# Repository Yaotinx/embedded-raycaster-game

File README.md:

# Real-Time Embedded 3D Raycaster Game

An ARM Cortex-M0+ based 3D Wolfenstein-style raycaster featuring real-time rendering on an ST7735 TFT display via SPI, custom fixed-point mathematics, and ISR-driven audio and control systems.

---

## 📌 Project Overview
This project implements a full 3D raycasting engine on a resource-constrained ARM Cortex-M0+ microcontroller without hardware floating-point support. The system uses fixed-point arithmetic to achieve a smooth 30Hz target render loop while handling simultaneous user inputs and hardware-driven audio.

---

## ⚙️ Technical Highlights

* **Fixed-Point Raycasting Engine:** Custom Digital Differential Analysis (DDA) ray marching and sprite rendering optimized for high-frame-rate rendering on a 128x160 ST7735 LCD display.
* **Interrupt-Driven Subsystems:** ISR-synchronized ADC sampling for analog joystick, potentiometer, and push-button controls to minimize input latency.
* **Audio & FSM Logic:** Dual-timer ISR DAC audio playback paired with a 4-state Finite State Machine (FSM) controlling game loops, dynamic difficulty scaling, and a randomized reward FIFO.
* **Graphics & Localization:** Custom font rendering supporting localized English and Japanese glyphs for game HUDs and menus.

---

## 🛠️ Hardware & Pinout Setup

* **Microcontroller:** ARM Cortex-M0+ (TI MSPM0)
* **Display:** ST7735 128x160 TFT Display (SPI Protocol)
* **Inputs:** 2-Axis Analog Joystick (ADC), Potentiometer (ADC), Direct Push Buttons
* **Audio:** R-2R Ladder DAC Output connected to an audio amplifier/speaker

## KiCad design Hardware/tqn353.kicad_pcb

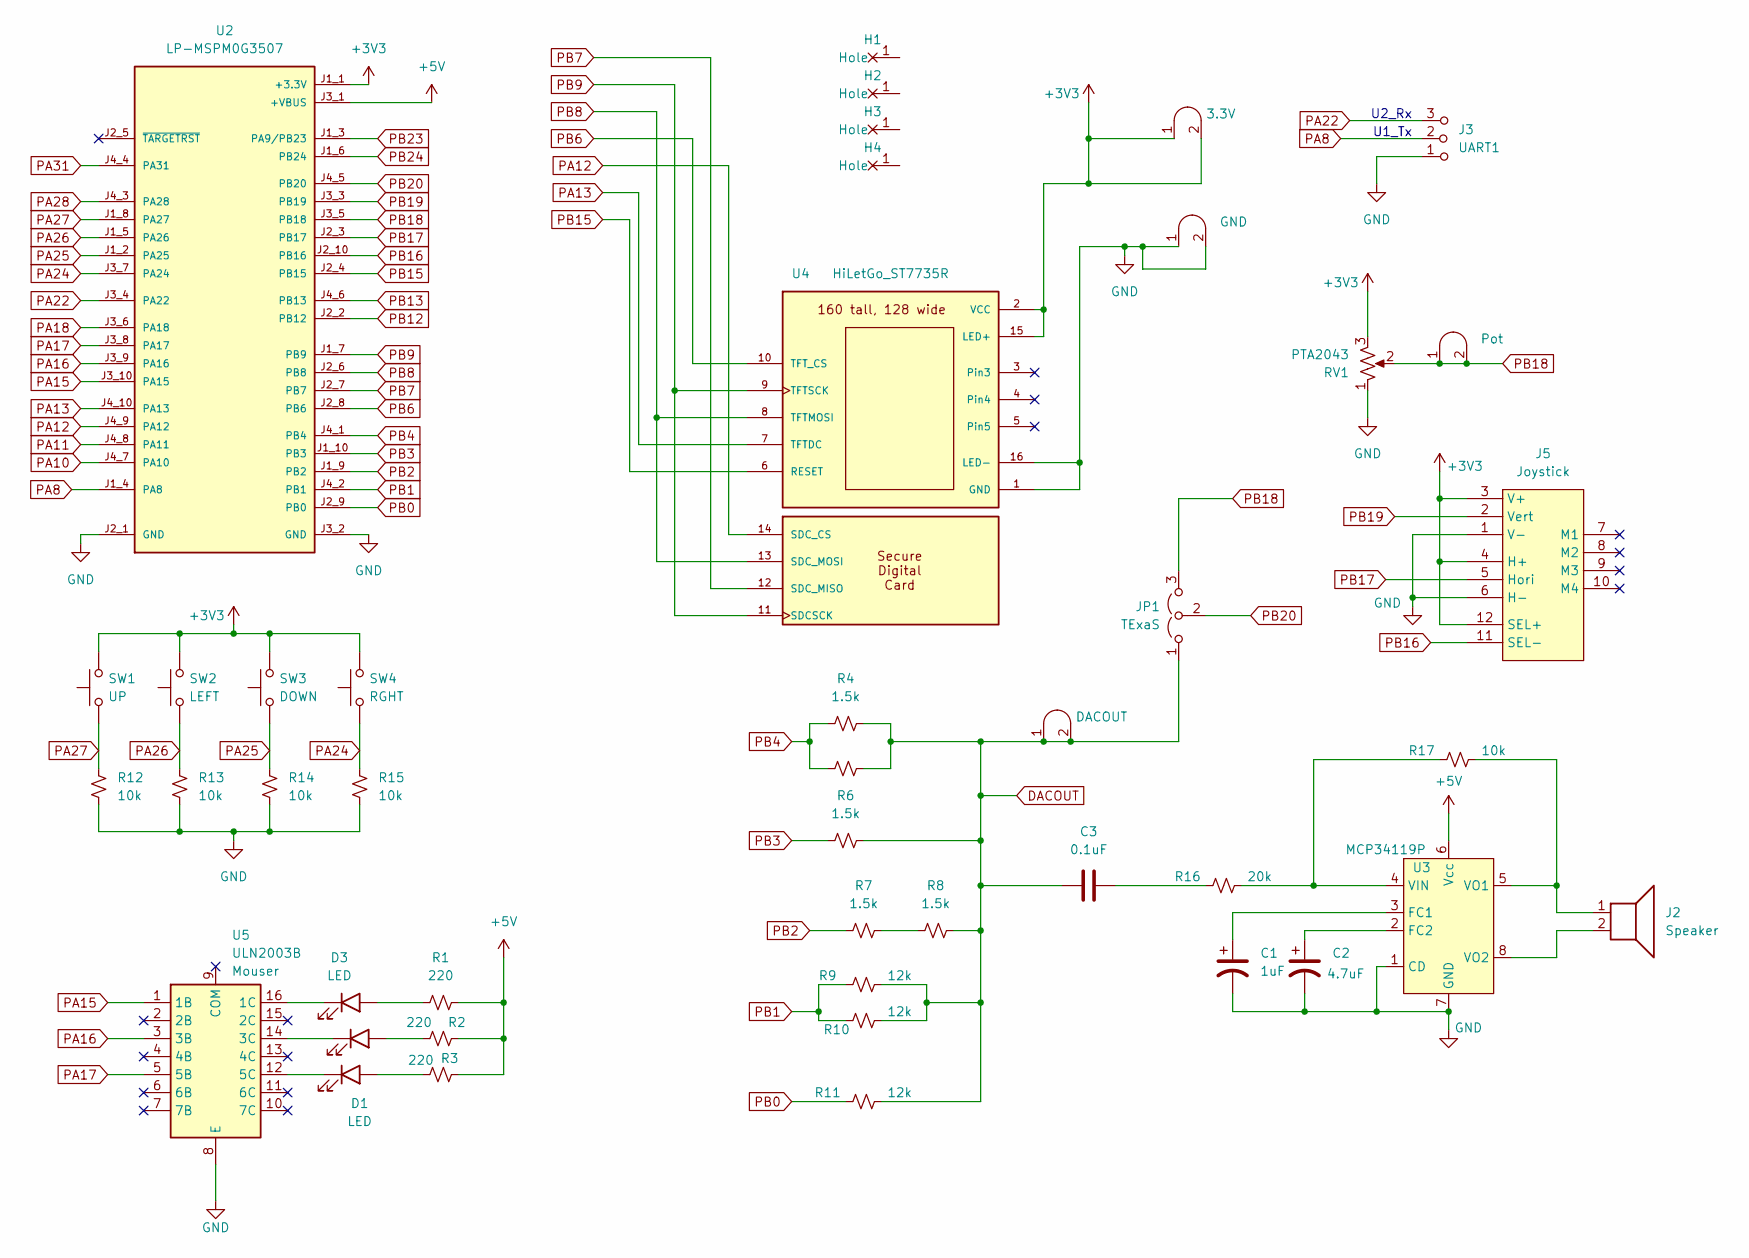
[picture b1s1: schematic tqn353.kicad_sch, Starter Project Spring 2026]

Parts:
C1: 1uF; CP_Radial_Tantal200mil
C2: 4.7uF; CP_Radial_Tantal200mil
C3: 0.1uF; C_Axial_200mil
D1, D2, D3: LED; LED_D5.0mm
H1, H2, H3, H4: MountingHole_4_40
J2: Speaker; PinHeader_1x02_P2.54mm_Vertical
J3: UART1; PinHeader_1x03_P2.54mm_Vertical
J4: Pot; Testpoint_1x02_P2.54mm
J5: Joystick; SparkfunJoystick
J6: GND; Testpoint_1x02_P2.54mm
J7: DACOUT; Testpoint_1x02_P2.54mm
JP1: TExaS; PinHeader_1x03_P2.54mm_Vertical
R1, R2, R3: 220; R_Axial_DIN0204_L3.6mm_D1.6mm_P7.62mm_Horizontal
R4, R5, R6, R7, R8: 1.5k; R_Axial_DIN0204_L3.6mm_D1.6mm_P7.62mm_Horizontal
R9, R10, R11: 12k; R_Axial_DIN0204_L3.6mm_D1.6mm_P7.62mm_Horizontal
R12, R13, R14, R15, R17: 10k; R_Axial_DIN0204_L3.6mm_D1.6mm_P7.62mm_Horizontal
R16: 20k; R_Axial_DIN0204_L3.6mm_D1.6mm_P7.62mm_Horizontal
RV1: PTA2043; PTA2043pot
SW1: UP; SW_PUSH_6mm
SW2: LEFT; SW_PUSH_6mm
SW3: DOWN; SW_PUSH_6mm
SW4: RGHT; SW_PUSH_6mm
TP1: 3.3V; Testpoint_1x02_P2.54mm
U2: LP-MSPM0G3507; ti_LP_MSPM0G3507
U3: MCP34119P; DIP-8_W7.62mm_LongPads
U4: HiLetGo_ST7735R; hiletgo_st7735r
U5: ULN2003B; DIP-16_W7.62mm

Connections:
+3V3: J5.3 (V+), J5.4 (H+), J5.12 (SEL+), RV1.3, SW1.2, SW2.2, SW3.2, SW4.2, TP1.1 (A), TP1.2 (B), U2.J1_1 (+3.3V), U4.2 (VCC), U4.15 (LED+)
+5V: R1.2, R2.2, R3.2, U2.J3_1 (+VBUS), U3.6 (Vcc)
DACOUT: C3.1, J7.1 (A), J7.2 (B), JP1.1 (A), R4.1, R5.1, R6.1, R8.1, R9.1, R10.1, R11.1
GND: C1.2, C2.2, J3.1 (A), J5.1 (V-), J5.6 (H-), J6.1 (A), J6.2 (B), R12.2, R13.2, R14.2, R15.2, RV1.1, U2.J2_1 (GND), U2.J3_2 (GND), U3.1 (CD), U3.7 (GND), U4.1 (GND), U4.16 (LED-), U5.8 (E)
unnamed: C3.2, R16.2
unnamed: D1.2 (A), R3.1
unnamed: D1.1 (K), U5.12 (5C)
unnamed: D2.2 (A), R2.1
unnamed: D2.1 (K), U5.14 (3C)
unnamed: D3.2 (A), R1.1
unnamed: D3.1 (K), U5.16 (1C)
unnamed: R7.1, R8.2
unnamed: C1.1, U3.3 (FC1)
unnamed: C2.1, U3.2 (FC2)
unnamed: R16.1, R17.2, U3.4 (VIN)
unnamed: J2.1, R17.1, U3.5 (VO1)
unnamed: J2.2, U3.8 (VO2)
PA8: J3.2 (B), U2.J1_4 (PA8)
PA10: U2.J4_7 (PA10)
PA11: U2.J4_8 (PA11)
PA12: U2.J4_9 (PA12), U4.14 (SDC_CS)
PA13: U2.J4_10 (PA13), U4.7 (TFTDC)
PA15: U2.J3_10 (PA15), U5.1 (1B)
PA16: U2.J3_9 (PA16), U5.3 (3B)
PA17: U2.J3_8 (PA17), U5.5 (5B)
PA18: U2.J3_6 (PA18)
PA22: J3.3 (C), U2.J3_4 (PA22)
PA24: R15.1, SW4.1, U2.J3_7 (PA24)
PA25: R14.1, SW3.1, U2.J1_2 (PA25)
PA26: R13.1, SW2.1, U2.J1_5 (PA26)
PA27: R12.1, SW1.1, U2.J1_8 (PA27)
PA28: U2.J4_3 (PA28)
PA31: U2.J4_4 (PA31)
PB0: R11.2, U2.J2_9 (PB0)
PB1: R9.2, R10.2, U2.J4_2 (PB1)
PB2: R7.2, U2.J1_9 (PB2)
PB3: R6.2, U2.J1_10 (PB3)
PB4: R4.2, R5.2, U2.J4_1 (PB4)
PB6: U2.J2_8 (PB6), U4.10 (TFT_CS)
PB7: U2.J2_7 (PB7), U4.12 (SDC_MISO)
PB8: U2.J2_6 (PB8), U4.8 (TFTMOSI), U4.13 (SDC_MOSI)
PB9: U2.J1_7 (PB9), U4.9 (TFTSCK), U4.11 (SDCSCK)
PB12: U2.J2_2 (PB12)
PB13: U2.J4_6 (PB13)
PB15: U2.J2_4 (PB15), U4.6 (RESET)
PB16: J5.11 (SEL-), U2.J2_10 (PB16)
PB17: J5.5 (Hori), U2.J2_3 (PB17)
PB18: J4.1 (A), J4.2 (B), JP1.3 (B), RV1.2, U2.J3_5 (PB18)
PB19: J5.2 (Vert), U2.J3_3 (PB19)
PB20: JP1.2 (C), U2.J4_5 (PB20)
PB23: U2.J1_3 (PA9/PB23)
PB24: U2.J1_6 (PB24)

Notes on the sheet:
U2_Rx
U1_Tx

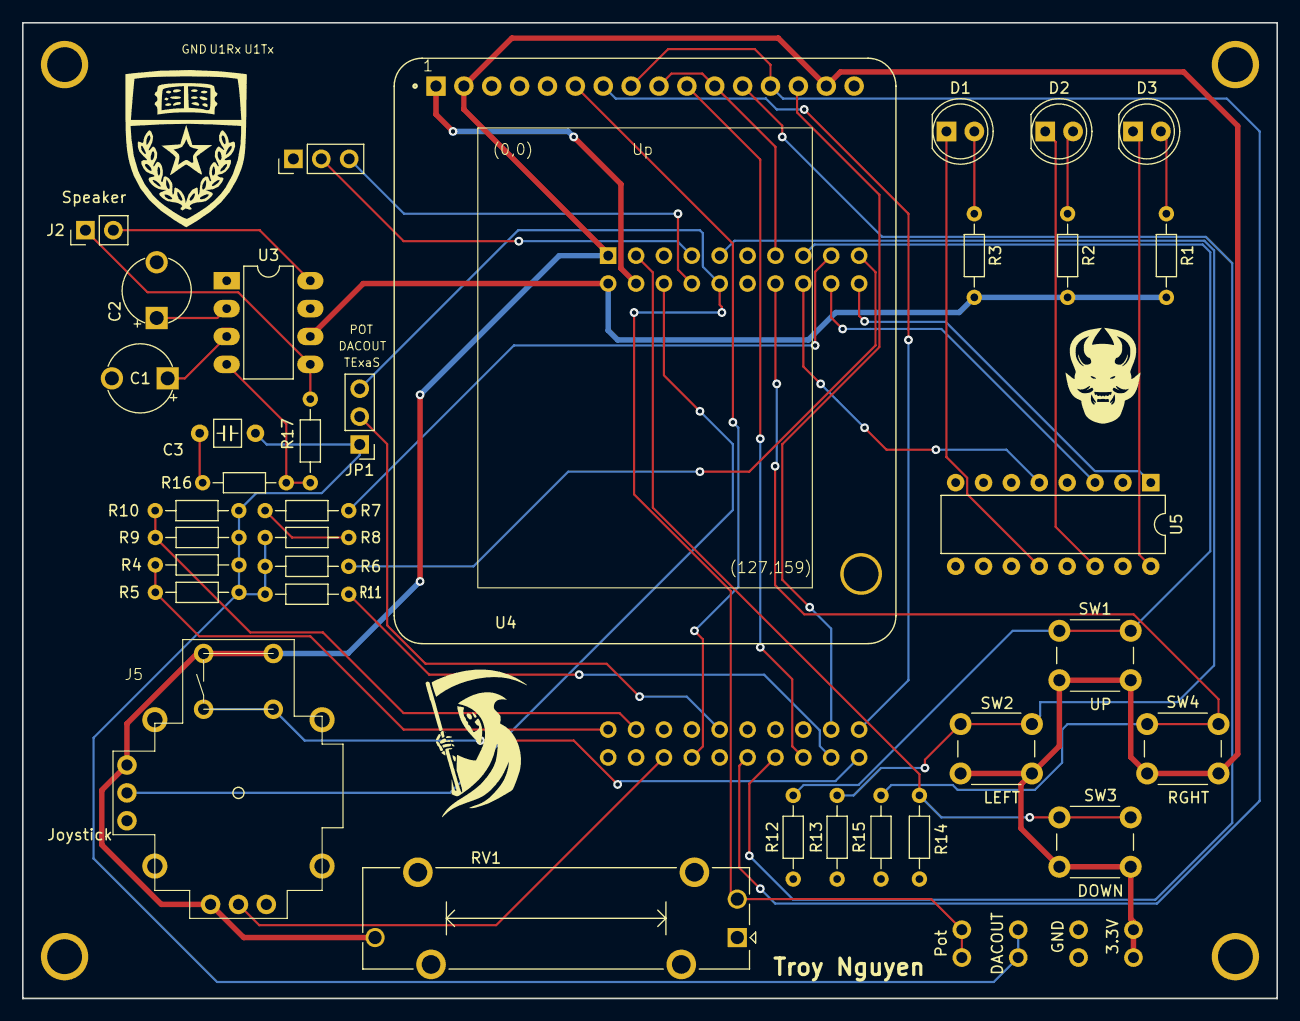
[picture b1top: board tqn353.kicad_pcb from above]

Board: 2 copper layers, 114.3 x 88.9 mm, 44 parts (1 on the bottom side), 43 nets.

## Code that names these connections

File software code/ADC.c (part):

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#include <stdint.h>
#include "../inc/ADC.h"
#include "../inc/Clock.h"
// PA27 ADC0 channel 0 J1.8 also MKII light interrupt
// PA26 ADC0 channel 1 J1.5 Joystick select button
// PA25 ADC0 channel 2 J1.2 MKII Joystick X
// PA24 ADC0 channel 3 J3.27 ***free***
// PB25 ADC0 channel 4 J19.7 (insert 0ohm R74, no U3 OPA2365)
// PB24 ADC0 channel 5 J1.6 MKII microphone in
// PB24 ADC0 channel 5 J1.6 TMP6131 PTC Thermistor 10k pullup J9 1-2, T (0.01C) = 2500+((n-2048)*2500)/337
// PB20 ADC0 channel 6 J4.36 ***free***
// PA22 ADC0 channel 7 J24 MKII Accelerometer Y
//
// PA15 ADC1 channel 0 J3.30 (also DACout)
// PA16 ADC1 channel 1 J3.29 ***free***
// PA17 ADC1 channel 2 J3.28 ***free***
// PA18 ADC1 channel 3 J3.26 MKII Joystick Y
// PB17 ADC1 channel 4 J2.18 ***free***
// PB18 ADC1 channel 5 J3.25 MKII Accelerometer Z
// PB19 ADC1 channel 6 J3.23 MKII Accelerometer X
// PA21 ADC1 channel 7 J17.8 (insert R20, remove R3)
// Assumes 40 MHz bus
void ADC0_Init(uint32_t channel, uint32_t reference){
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
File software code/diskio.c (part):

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// **********ST7735 TFT and SDC*******************
// ST7735
// Backlight (pin 10)     to +3.3 V
// MISO (pin 9)           to SPI1 POCI: PB7
// SCK (pin 8)            to SPI1 SCLK: PB9
// MOSI (pin 7)           to SPI1 PICO: PB8
// TFT_CS (pin 6)         to GPIO:  PB6
// CARD_CS (pin 5)        to PA12 (GPIO)
// Data/Command (pin 4)   to PA13 (GPIO), high for data, low for command
// RESET (pin 3)          to PB15 (GPIO)
// VCC (pin 2)            to +3.3 V
// Gnd (pin 1)            to ground

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// ST7735
// LED-   (pin 16) TFT, to ground
// LED+   (pin 15) TFT, to +3.3 V
// SD_CS  (pin 14) SDC, to PA12 chip select
// MOSI   (pin 13) SDC, to PB8 MOSI
// MISO   (pin 12) SDC, to PB7 MISO
// SCK    (pin 11) SDC, to serial clock
// CS     (pin 10) TFT, to PB6  GPIO
// SCL    (pin 9)  TFT, to PB9  SPI1 SCLK
// SDA    (pin 8)  TFT, to PB8  MOSI SPI1 PICO
// A0     (pin 7)  TFT, to PA13 Data/Command, high for data, low for command
// RESET  (pin 6)  TFT, to PB15 reset (GPIO), low to reset
// NC     (pins 3,4,5)
// VCC    (pin 2)       to +3.3 V
// GND    (pin 1)       to ground

#define TFT_CS_LOW()     (GPIOB->DOUTCLR31_0 = (1<<6))   // PB6 low
#define TFT_CS_HIGH()    (GPIOB->DOUTSET31_0 = (1<<6))   // PB6 high

// PA12 output used for SDC CS
#if SDC_CS_PA12
#define SDC_CS           GPIOA
#define SDC_CS_PIN       (1<<12)         // CS controlled by software
#define SDC_CS_LOW()     (SDC_CS->DOUTCLR31_0 = SDC_CS_PIN)   // PA12 low
#define SDC_CS_HIGH()    (SDC_CS->DOUTSET31_0 = SDC_CS_PIN)   // PA12 high
void CS_Init(void){
  IOMUX->SECCFG.PINCM[PA12INDEX]  = (uint32_t) 0x00000081;
  SDC_CS->DOE31_0 |= SDC_CS_PIN;
  SDC_CS_HIGH(); // PA12=1
}
#endif
//********SPI1_Init*****************
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      //   bits 31-24 unlock key 0x26
      //   bit 0 is Enable Power
  SPI1->GPRCM.PWREN = 0x26000001;
    // configure PB9 PB6 PB8 as alternate SPI1 function
  IOMUX->SECCFG.PINCM[PB9INDEX]  = 0x00000083;  // SPI1 SCLK
  //  IOMUX->SECCFG.PINCM[PB6INDEX]  = 0x00000083;  // SPI1 CS0
  IOMUX->SECCFG.PINCM[PB8INDEX]  = 0x00000083;  // SPI1 PICO
  IOMUX->SECCFG.PINCM[PB15INDEX] = 0x00000081;  // GPIO output, LCD !RST
  IOMUX->SECCFG.PINCM[PA13INDEX] = 0x00000081;  // GPIO output, LCD RS
  IOMUX->SECCFG.PINCM[PB7INDEX]  = 0x00040083;  // SPI1 POCI
  IOMUX->SECCFG.PINCM[PB6INDEX]  = 0x00000081;  // PB6 is regular GPIO
  Clock_Delay(24); // time for gpio to power up
  GPIOA->DOE31_0 |= 1<<13;    // PA13 is LCD RS
  GPIOB->DOE31_0 |= 1<<15;    // PB15 is LCD !RST
  GPIOA->DOUTSET31_0 = 1<<13; // RS=1
  GPIOB->DOUTSET31_0 = 1<<15; // !RST = 1
  GPIOB->DOE31_0 |= 1<<6;     // PB6 is regular GPIO
  SPI1->CLKSEL = 8; // SYSCLK
  // bit 3 SYSCLK
  // bit 2 MFCLK
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

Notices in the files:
software code/diskio.c:
Copyright (C) 2014, ChaN, all right reserved.
